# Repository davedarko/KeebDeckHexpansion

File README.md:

# Keebdexpansion

A keyboard hexpansion for the [Tildagon badge](https://tildagon.badge.emfcamp.org/) using the [solder.party KeebDeck Keyboard](https://www.solder.party/docs/keebdeck/keyboard/). Software for the hexpansion is [provided by @sodoku](https://github.com/sodoku/tildagon-keebdexpansion).

## Features

- Full layout keyboard
- RGB-Backlit keys
- Type in text inputs

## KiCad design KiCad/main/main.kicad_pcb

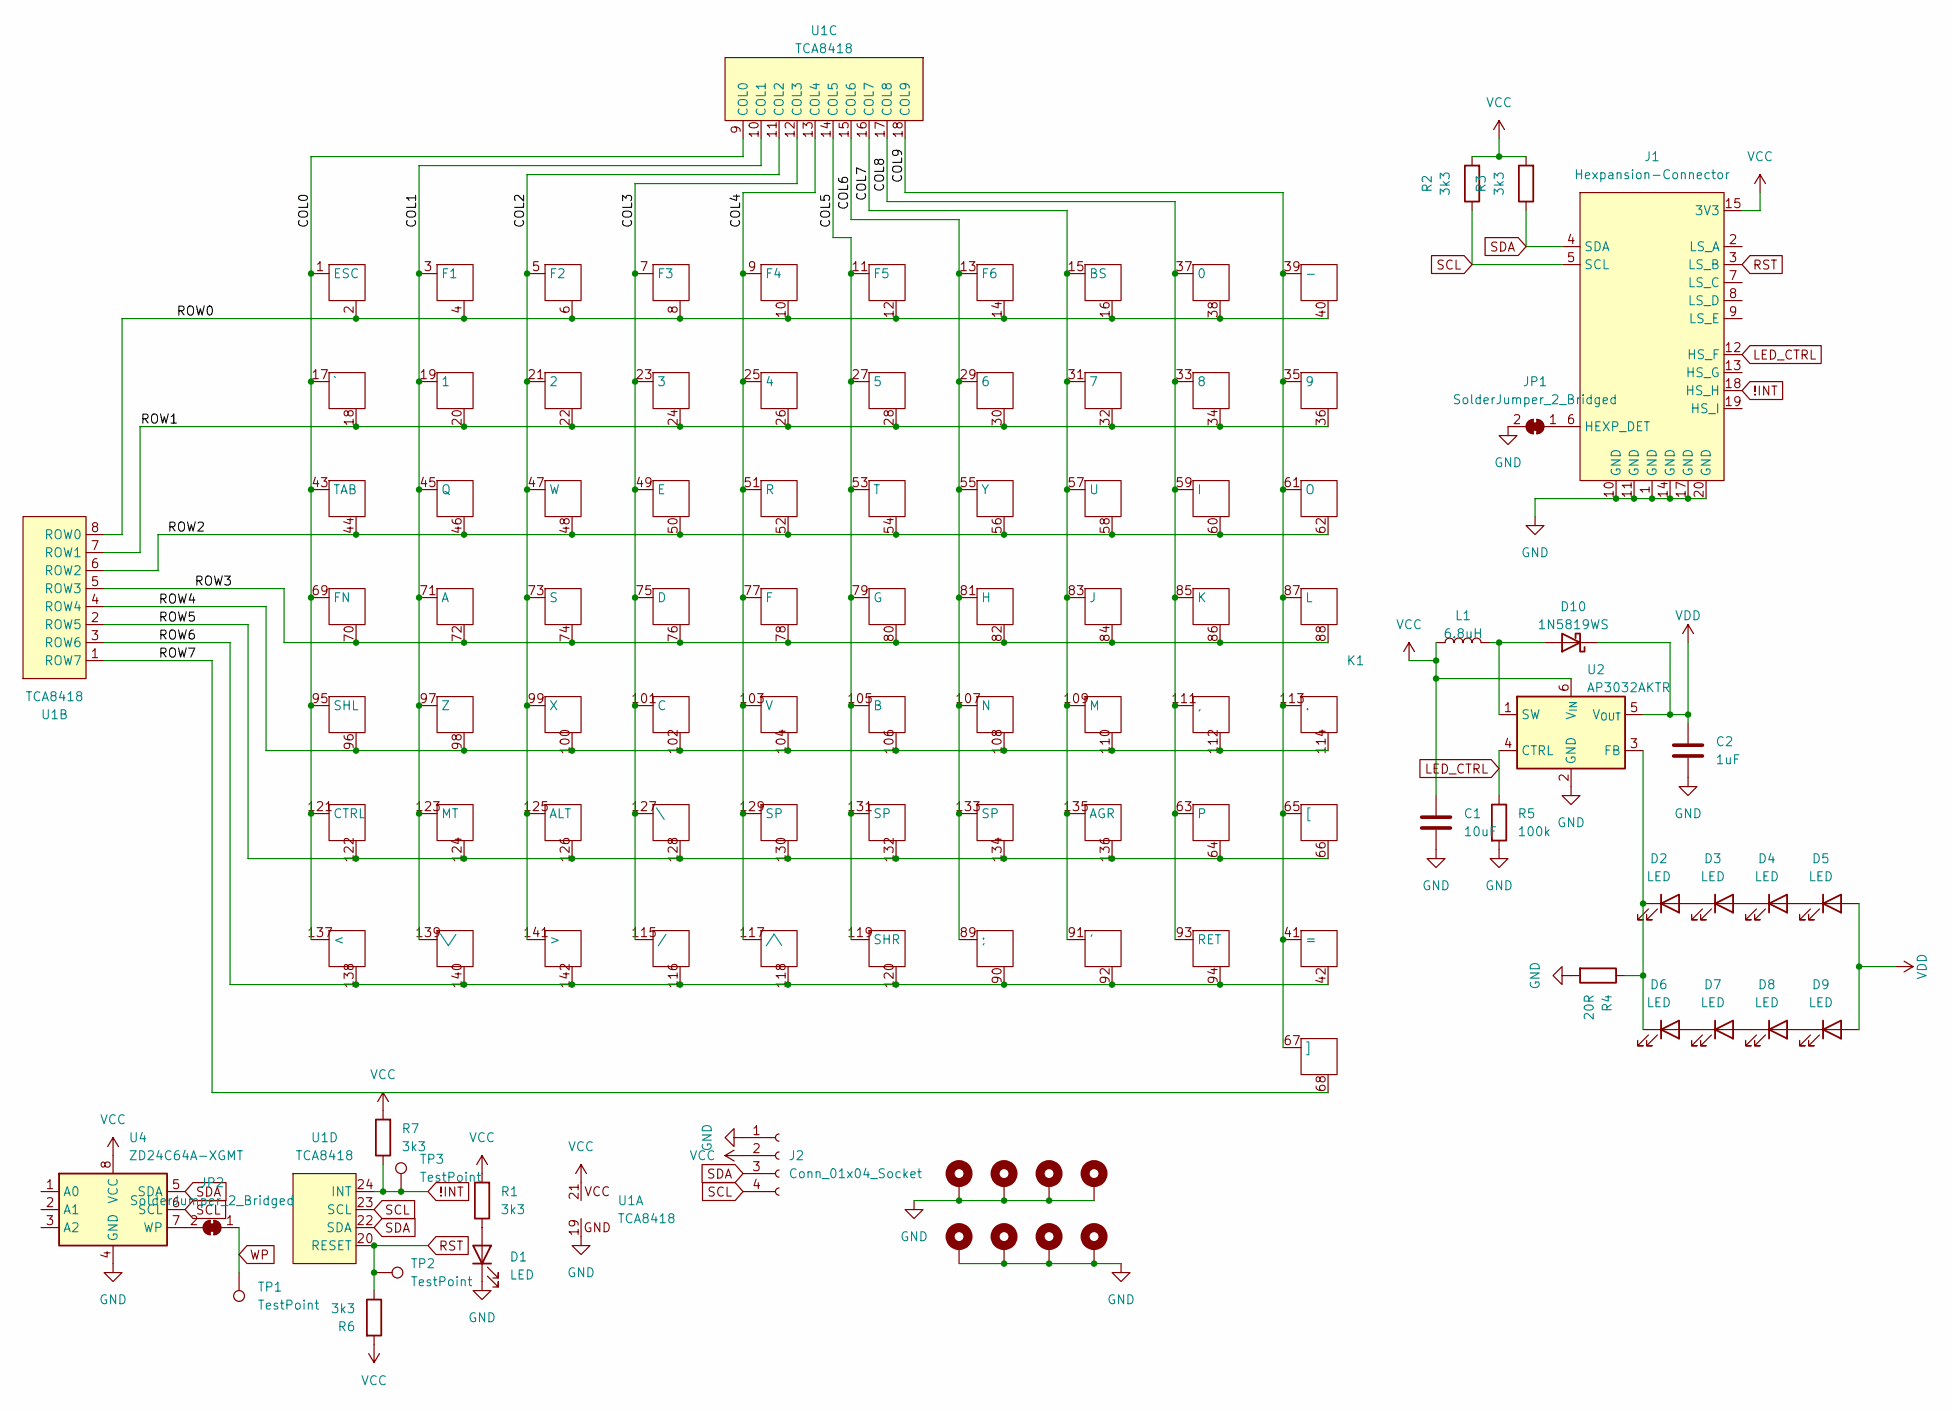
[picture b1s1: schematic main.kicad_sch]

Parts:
C1: 10uF; C_0603_1608Metric_Pad1.08x0.95mm_HandSolder
C2: 1uF; C_0603_1608Metric_Pad1.08x0.95mm_HandSolder
D1: LED; LED_0603_1608Metric_Pad1.05x0.95mm_HandSolder
D2, D3, D4, D5, D6, D7, D8, D9: LED; LTW-010DCG; LCSC C575429
D10: 1N5819WS; D_SOD-323
H1, H2, H3, H4: MountingHole_Pad; MountingHole_2.2mm_M2_Pad_Via
H5, H6, H7, H8: MountingHole_Pad; MountingHole_2.2mm_M2_Pad_Via; LCSC C2915626
J1: Hexpansion-Connector; hexpansion-edge-connector
J2: Conn_01x04_Socket; JST_SH_SM04B-SRSS-TB_1x04-1MP_P1.00mm_Horizontal
JP1, JP2: SolderJumper_2_Bridged; SolderJumper-2_P1.3mm_Bridged_RoundedPad1.0x1.5mm
K1: keyboard_arturo182
L1: 6.8uH; L_0603_1608Metric_Pad1.05x0.95mm_HandSolder
R1, R2, R3, R6, R7: 3k3; R_0603_1608Metric_Pad0.98x0.95mm_HandSolder
R4: 20R; R_0603_1608Metric_Pad0.98x0.95mm_HandSolder
R5: 100k; R_0603_1608Metric_Pad0.98x0.95mm_HandSolder
TP1, TP2, TP3: TestPoint; TestPoint_Pad_D1.5mm
U1: TCA8418; QFN50P400X400X80-25N
U2: AP3032AKTR; SOT-23-6; LCSC C264086
U4: ZD24C64A-XGMT; TSSOP-8_4.4x3mm_P0.65mm; MPN C2875852

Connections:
!INT: J1.18 (HS_H), R7.1, TP3.1, U1.24 (INT)
/COL0: K1.1 (ESC), K1.17 (`), K1.43 (TAB), K1.69 (FN), K1.95 (SHL), K1.121 (CTRL), K1.137 (<), U1.9 (COL0)
/COL1: K1.3 (F1), K1.19 (1), K1.45 (Q), K1.71 (A), K1.97 (Z), K1.123 (MT), K1.139 (\/), U1.10 (COL1)
/COL2: K1.5 (F2), K1.21 (2), K1.47 (W), K1.73 (S), K1.99 (X), K1.125 (ALT), K1.141 (>), U1.11 (COL2)
/COL3: K1.7 (F3), K1.23 (3), K1.49 (E), K1.75 (D), K1.101 (C), K1.115 (/), K1.127 (\), U1.12 (COL3)
/COL4: K1.9 (F4), K1.25 (4), K1.51 (R), K1.77 (F), K1.103 (V), K1.117 (/\), K1.129 (SP), U1.13 (COL4)
/COL5: K1.11 (F5), K1.27 (5), K1.53 (T), K1.79 (G), K1.105 (B), K1.119 (SHR), K1.131 (SP), U1.14 (COL5)
/COL6: K1.13 (F6), K1.29 (6), K1.55 (Y), K1.81 (H), K1.89 (;), K1.107 (N), K1.133 (SP), U1.15 (COL6)
/COL7: K1.15 (BS), K1.31 (7), K1.57 (U), K1.83 (J), K1.91 ('), K1.109 (M), K1.135 (AGR), U1.16 (COL7)
/COL8: K1.33 (8), K1.37 (0), K1.59 (I), K1.63, K1.85 (K), K1.93 (RET), K1.111 (,), U1.17 (COL8)
/COL9: K1.35 (9), K1.39 (-), K1.41 (=), K1.61 (O), K1.65 ([), K1.67 (]), K1.87 (L), K1.113 (.), U1.18 (COL9)
/ROW0: K1.2, K1.4, K1.6, K1.8, K1.10, K1.12, K1.14, K1.16, K1.38, K1.40, U1.8 (ROW0)
/ROW1: K1.18, K1.20, K1.22, K1.24, K1.26, K1.28, K1.30, K1.32, K1.34, K1.36, U1.7 (ROW1)
/ROW2: K1.44, K1.46, K1.48, K1.50, K1.52, K1.54, K1.56, K1.58, K1.60, K1.62, U1.6 (ROW2)
/ROW3: K1.70, K1.72, K1.74, K1.76, K1.78, K1.80, K1.82, K1.84, K1.86, K1.88, U1.5 (ROW3)
/ROW4: K1.96, K1.98, K1.100, K1.102, K1.104, K1.106, K1.108, K1.110, K1.112, K1.114, U1.4 (ROW4)
/ROW5: K1.64, K1.66, K1.122, K1.124, K1.126, K1.128, K1.130, K1.132, K1.134, K1.136, U1.2 (ROW5)
/ROW6: K1.42, K1.90, K1.92, K1.94, K1.116, K1.118, K1.120, K1.138, K1.140, K1.142, U1.3 (ROW6)
/ROW7: K1.68, U1.1 (ROW7)
GND: C1.2, C2.2, D1.1 (K), H1.1, H2.1, H3.1, H4.1, H5.1, H6.1, H7.1, H8.1, J1.1 (GND), J1.10 (GND), J1.11 (GND), J1.14 (GND), J1.17 (GND), J1.20 (GND), J2.1, JP1.2 (B), R4.2, R5.2, U1.19, U2.2 (GND), U4.4 (GND)
LED_CTRL: J1.12 (HS_F), R5.1, U2.4 (CTRL)
unnamed: D1.2 (A), R1.1
unnamed: D2.2 (A), D3.1 (K)
unnamed: D2.1 (K), D6.1 (K), R4.1, U2.3 (FB)
unnamed: D3.2 (A), D4.1 (K)
unnamed: D4.2 (A), D5.1 (K)
unnamed: D6.2 (A), D7.1 (K)
unnamed: D7.2 (A), D8.1 (K)
unnamed: D8.2 (A), D9.1 (K)
unnamed: D10.2 (A), L1.2, U2.1 (SW)
unnamed: J1.6 (HEXP_DET), JP1.1 (A)
unnamed: JP2.2 (B), U4.7 (WP)
RST: J1.3 (LS_B), R6.1, TP2.1, U1.20 (RESET)
SCL: J1.5 (SCL), J2.4, R2.1, U1.23 (SCL), U4.6 (SCL)
SDA: J1.4 (SDA), J2.3, R3.1, U1.22 (SDA), U4.5 (SDA)
VCC: C1.1, J1.15 (3V3), J1.16 (3V3), J2.2, L1.1, R1.2, R2.2, R3.2, R6.2, R7.2, U1.21, U2.6 (V_{IN}), U4.8 (VCC)
VDD: C2.1, D5.2 (A), D9.2 (A), D10.1 (K), U2.5 (V_{OUT})
WP: JP2.1 (A), TP1.1

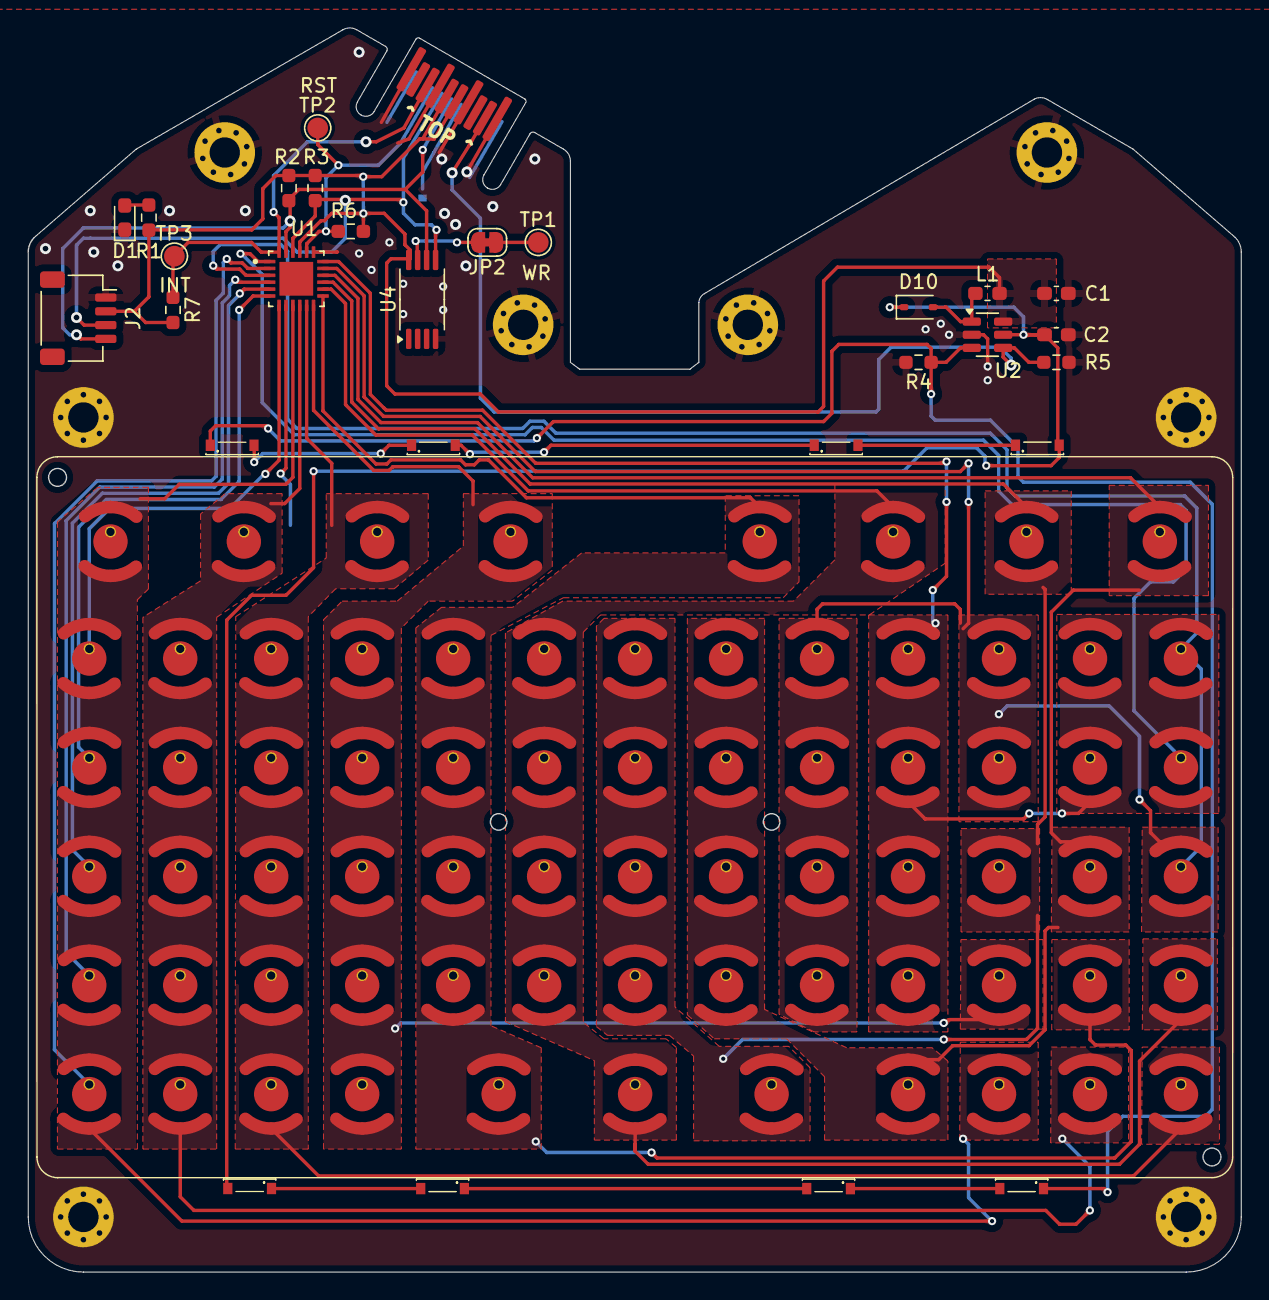
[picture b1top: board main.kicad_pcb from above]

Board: 2 copper layers, 88.0 x 90.2 mm, 39 parts (1 on the bottom side), 38 nets.

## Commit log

2025-11-20 deploy design files V0.1
2026-01-08 fixed missing connections and changed eeprom
2026-04-12 Updated board designs to mirror hardware choices
2026-04-23 Add more pizzaz and changelog
2026-04-24 Test App for PWM LED control
2026-05-06 Revert "Test App for PWM LED control"
    This reverts commit 16f5d63235216fa5ad93ad454a595f19e9ea91df.
2026-05-06 _final_final_last_now_1
2026-05-30 Change name to keepdexpansion
